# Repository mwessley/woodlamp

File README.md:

# woodlamp

## First Render of the Lamp

## PCB Layout

## BOM

- Akku 2 Standard cell
- 
- 
- 
- npn Transistor

## TODO
- Ladeschaltung (Extended Board v2)
- Adapt 3D Prints

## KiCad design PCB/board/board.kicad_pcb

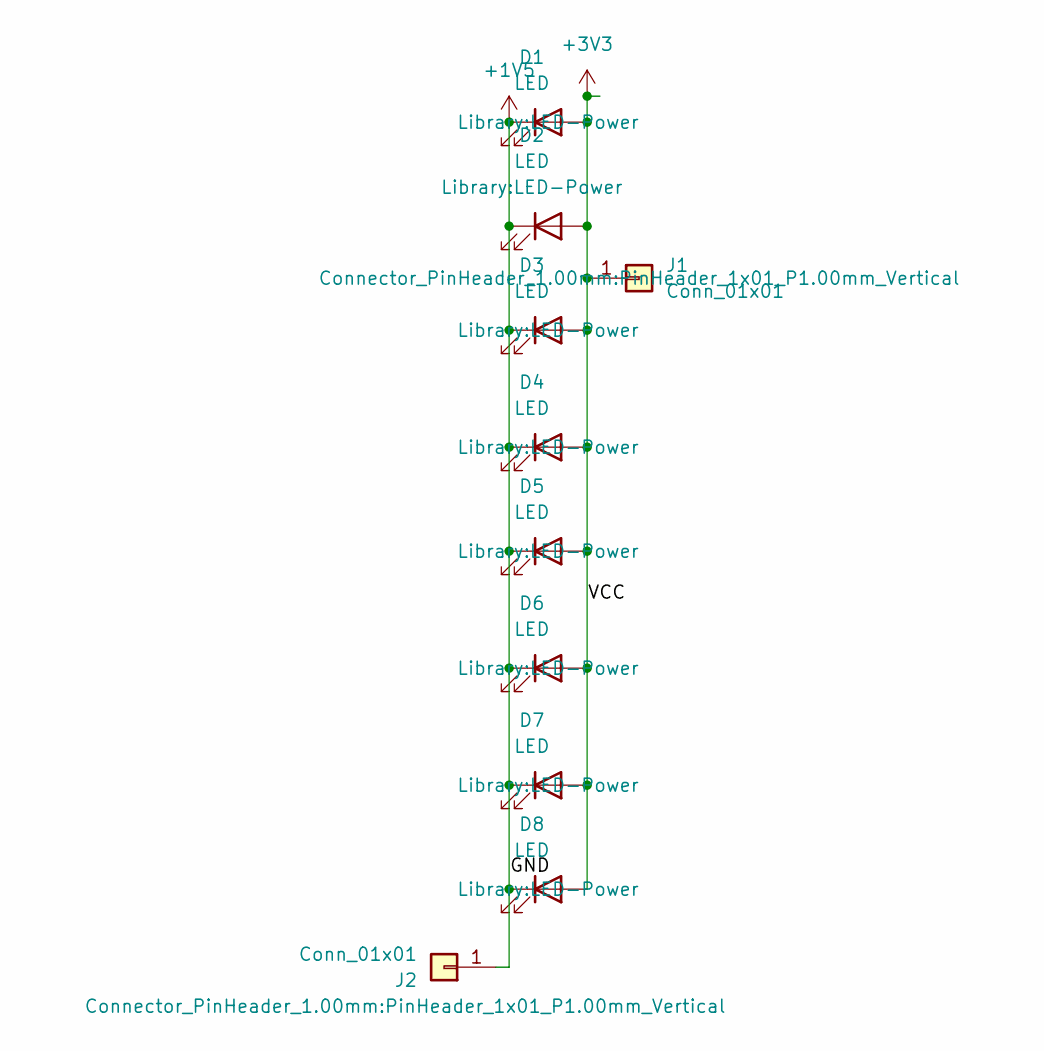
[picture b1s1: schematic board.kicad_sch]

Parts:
D1, D2, D3, D4, D5, D6, D7, D8: LED; LED-Power
J1, J2: Conn_01x01; PinHeader_1x01_P1.00mm_Vertical

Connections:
+1V5: D1.1 (K), D2.1 (K), D3.1 (K), D4.1 (K), D5.1 (K), D6.1 (K), D7.1 (K), D8.1 (K), J2.1
+3V3: D1.2 (A), D2.2 (A), D3.2 (A), D4.2 (A), D5.2 (A), D6.2 (A), D7.2 (A), D8.2 (A), J1.1

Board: 2 copper layers, 10 parts (0 on the bottom side), 2 nets, no tracks yet.

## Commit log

2022-12-09 Inital current state commit
2023-01-07 updated 3D models
